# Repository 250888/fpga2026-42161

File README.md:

# 瞬迹（XunJi）— 基于 FPGA 的线束拓扑重建与 μs 级瞬态开路诊断装置

> 主控：EGO1 **Artix-7 XC7A35T-1CSG324C** @ 100 MHz ｜ 工具链：**Vivado 2026.1**
> 赛事：第十届全国大学生嵌入式芯片与系统设计竞赛 · FPGA 创新设计赛道（AMD）
> 许可证：[MIT](LICENSE)
> 大模型协作记录：[`report/llm-collaboration-log.md`](report/llm-collaboration-log.md) ｜ 技能包：[`skill/`](skill/)

## 一句话主线

**静态重建「线怎么接」，动态捕获「线什么时候断」。**

16 路逐路扫描重建 16×16 连接矩阵；与学习到的参考矩阵比对，输出五级故障判定
（PASS / OPEN / MISWIRE / BRIDGE / ANOMALY）并定位到具体线号；
再由 CD4066 阵列注入 μs 级瞬态断线，FPGA 以 100 MHz 采样捕获。

## 实测指标

| 指标 | 值 |
|---|---|
| 通道数 | 16 |
| 单轮扫描周期 | 112 μs |
| 帧长 / 波特率 / 帧率 | 48 B / 115200 bps / 240 fps |
| 资源（XC7A35T） | LUT **2119**（10.19%）· FF **1564**（3.76%）· BRAM 0 · DSP 0 |
| 时序 | WNS **+1.408 ns**，全部约束满足 |
| 回归 | iverilog 6/6 testbench · pytest **84** 项 |
| 实测结果 | 16/16 通道全通；四类故障（拔线/接反/短接/混合）全部正确分类并定位 |

## 快速开始

```bat
uv sync                                   :: 安装依赖（Python 3.12）
uv run pytest -q                          :: 全部测试（84 项）
uv run python -m xunji.cli sim            :: iverilog 仿真（6 个 testbench）
uv run python -m xunji.cli lint           :: RTL 风格检查
uv run python scripts\sync_to_build.py --build   :: 综合+实现，产出 .bit
```

> 注意：本机部分环境下 `uv run xunji` 启动器会被策略拦截，
> 请统一用 `uv run python -m xunji.cli <子命令>`。

烧录（EGO1，JTAG）：

```bat
C:\AMDDesignTools\2026.1\Vivado\bin\vivado.bat -mode batch -source scripts\program_ego1.tcl
```

> ⚠ JTAG 配置是**易失**的：每次断电/重新插拔后必须重新烧录。
> 且 LEARN 的参考矩阵存在 FPGA 寄存器里，重烧后需重新按学习键（板载 **S1**）。

## 目录结构

主办方推荐结构见指南 §3.3.5.4；本仓库**保留中文目录名**（更贴合队内协作习惯），
按指南「采用其他组织方式须给出目录对照说明」的要求对照如下：

| 本项目路径 | 作用 | 对应推荐结构 |
|---|---|---|
| `rtl/` | Verilog 源码（15 个文件） | `src/` |
| `sim/` | testbench（6 个） | `sim/` |
| `tests/` | pytest（84 项，含黄金帧回归） | `sim/`（验证） |
| `src/xunji/` | 主机侧 Python 包（协议解析 / CLI） | `src/`（软件） |
| `constrs/` | EGO1 XDC | `build/` |
| `scripts/` | Vivado Tcl · 构建 · 报告与海报生成 · 烧录 | `build/` |
| `pcb/` | 前端板参数化生成脚本 + KiCad 工程 + Gerber | `board/`（自制硬件） |
| `firmware/` | Arduino Nano 4066 脉冲源固件 | `board/` |
| `doc/` | 设计报告、上位机、证据 hex、原理图与 PCB 图、外壳模型 | `report/` + `data/` |
| **`skill/`** | **技能包（指南要求）** | `skill/` |
| **`report/`** | **大模型协作记录（指南要求）** | `report/` |

## 关键设计

### 双端有源扫描拓扑

```
a_ctrl_n → LVC07(开漏) → RS 330Ω → JA → 被测线束 → JB → RP 4.7kΩ 上拉
        → LVC14(施密特反相) → b_raw → FPGA
```

- A 端开漏激励：多路同时存在时不会发生推挽竞争；串阻把单路短路电流限制在约 10 mA
- B 端上拉 + 施密特反相：抑制长线束慢边沿抖动
- 仅用 32 根信号线完成 16×16 全连接矩阵重建

### 三层滤波

空闲稳定窗 500 周期（5 μs）→ 101 拍多数表决 → 8 拍去毛刺。

### 单时钟、纯 clock-enable

全系统仅 100 MHz 一个时钟域；`b_raw` / `uart_rx` 均经两级同步器；
复位经异步拉低、同步释放。

### 帧矩阵快照

在发送触发沿锁存矩阵，保证一帧内 CRC 与负载**同源**（这是本项目最重要的一个缺陷修复）。

## 故障判定语义

| cls | 含义 | 判据 |
|---|---|---|
| 0 | PASS | 与参考矩阵完全一致 |
| 3 | BRIDGE | 任一方向度 > 1（短接优先） |
| 2 | MISWIRE | 有缺失也有额外，且仍是双射（接反/换位） |
| 1 | OPEN | 只有缺失、没有额外，且缺失行实测为空 |
| 4 | ANOMALY | 混合、无法唯一解释（**不夸大**：拒绝硬套类型） |
| 5 | NO_REF | 尚未学习 |

## 硬件

- **主控**：EGO1（XC7A35T），100 MHz → P17，复位 P15，UART T4/N5
- **前端板 FE-16**：96×96 mm 双层板，LVC07×3 + LVC14×3 + 49 颗电阻 + 7 颗电容，
  JA/JB 为 2×10 接口，J5 2×18 与主控对接，TP1–TP50 测试点
- **故障注入**：CD4066 ×4（32 路开关）+ Arduino Nano

## 复现步骤（从零开始）

1. **装环境**：Python 3.12 + `uv`；Vivado 2026.1
2. **拉代码**：`git clone <repo>` → `uv sync`
3. **验软件**：`uv run pytest -q`（应 84 passed）→ `uv run python -m xunji.cli sim`（应 6/6 PASS）
4. **做硬件**：按 `pcb/frontend16/` 的脚本生成 Gerber 打板并焊装（BOM 见 `doc/`）
5. **出 bit**：`uv run python scripts\sync_to_build.py --build`
6. **上板**：烧录 `program_ego1.tcl` → 拨扫描开关 → 串口 115200 收帧
7. **学参考**：接 1:1 线束全通后，按板载 **S1** 学习 → `cls` 由 5 变 0
8. **做故障**：拔线 → `cls=1`；交换两根 → `cls=2`；短接两根 → `cls=3`
9. **看结果**：`uv run python -m xunji.cli read --port COM<x> --frames 3`

## 文档索引

| 文件 | 内容 |
|---|---|
| [`report/llm-collaboration-log.md`](report/llm-collaboration-log.md) | 大模型协作记录（提示词 / 自我纠错轨迹 / 失误清单） |
| [`skill/README.md`](skill/README.md) | 技能包索引与复用验证 |
| `doc/瞬迹_作品报告.pdf` | 作品设计报告（提交版） |
| `doc/瞬迹_海报_中英_终版.pptx` | **提交用海报（定稿，中英各一页）** |
| `doc/瞬迹_海报_中文版_含校徽.pdf` · `doc/XUNJI_Poster_English_含校徽.pdf` | 海报的 PDF 定稿（含校徽与队伍信息，仅用于上传与展示；决赛现场 A4 打印版需去掉队伍信息） |
| `doc/证据/` | 四类故障的原始帧证据（hex） |
| `doc/photous/` | 实物照片与演示截图 |
| `AGENTS.md` | 开发规范（AI 协作者必读） |

## 许可证

[MIT](LICENSE) —— 允许再分发，欢迎复用 `skill/` 中的经验。

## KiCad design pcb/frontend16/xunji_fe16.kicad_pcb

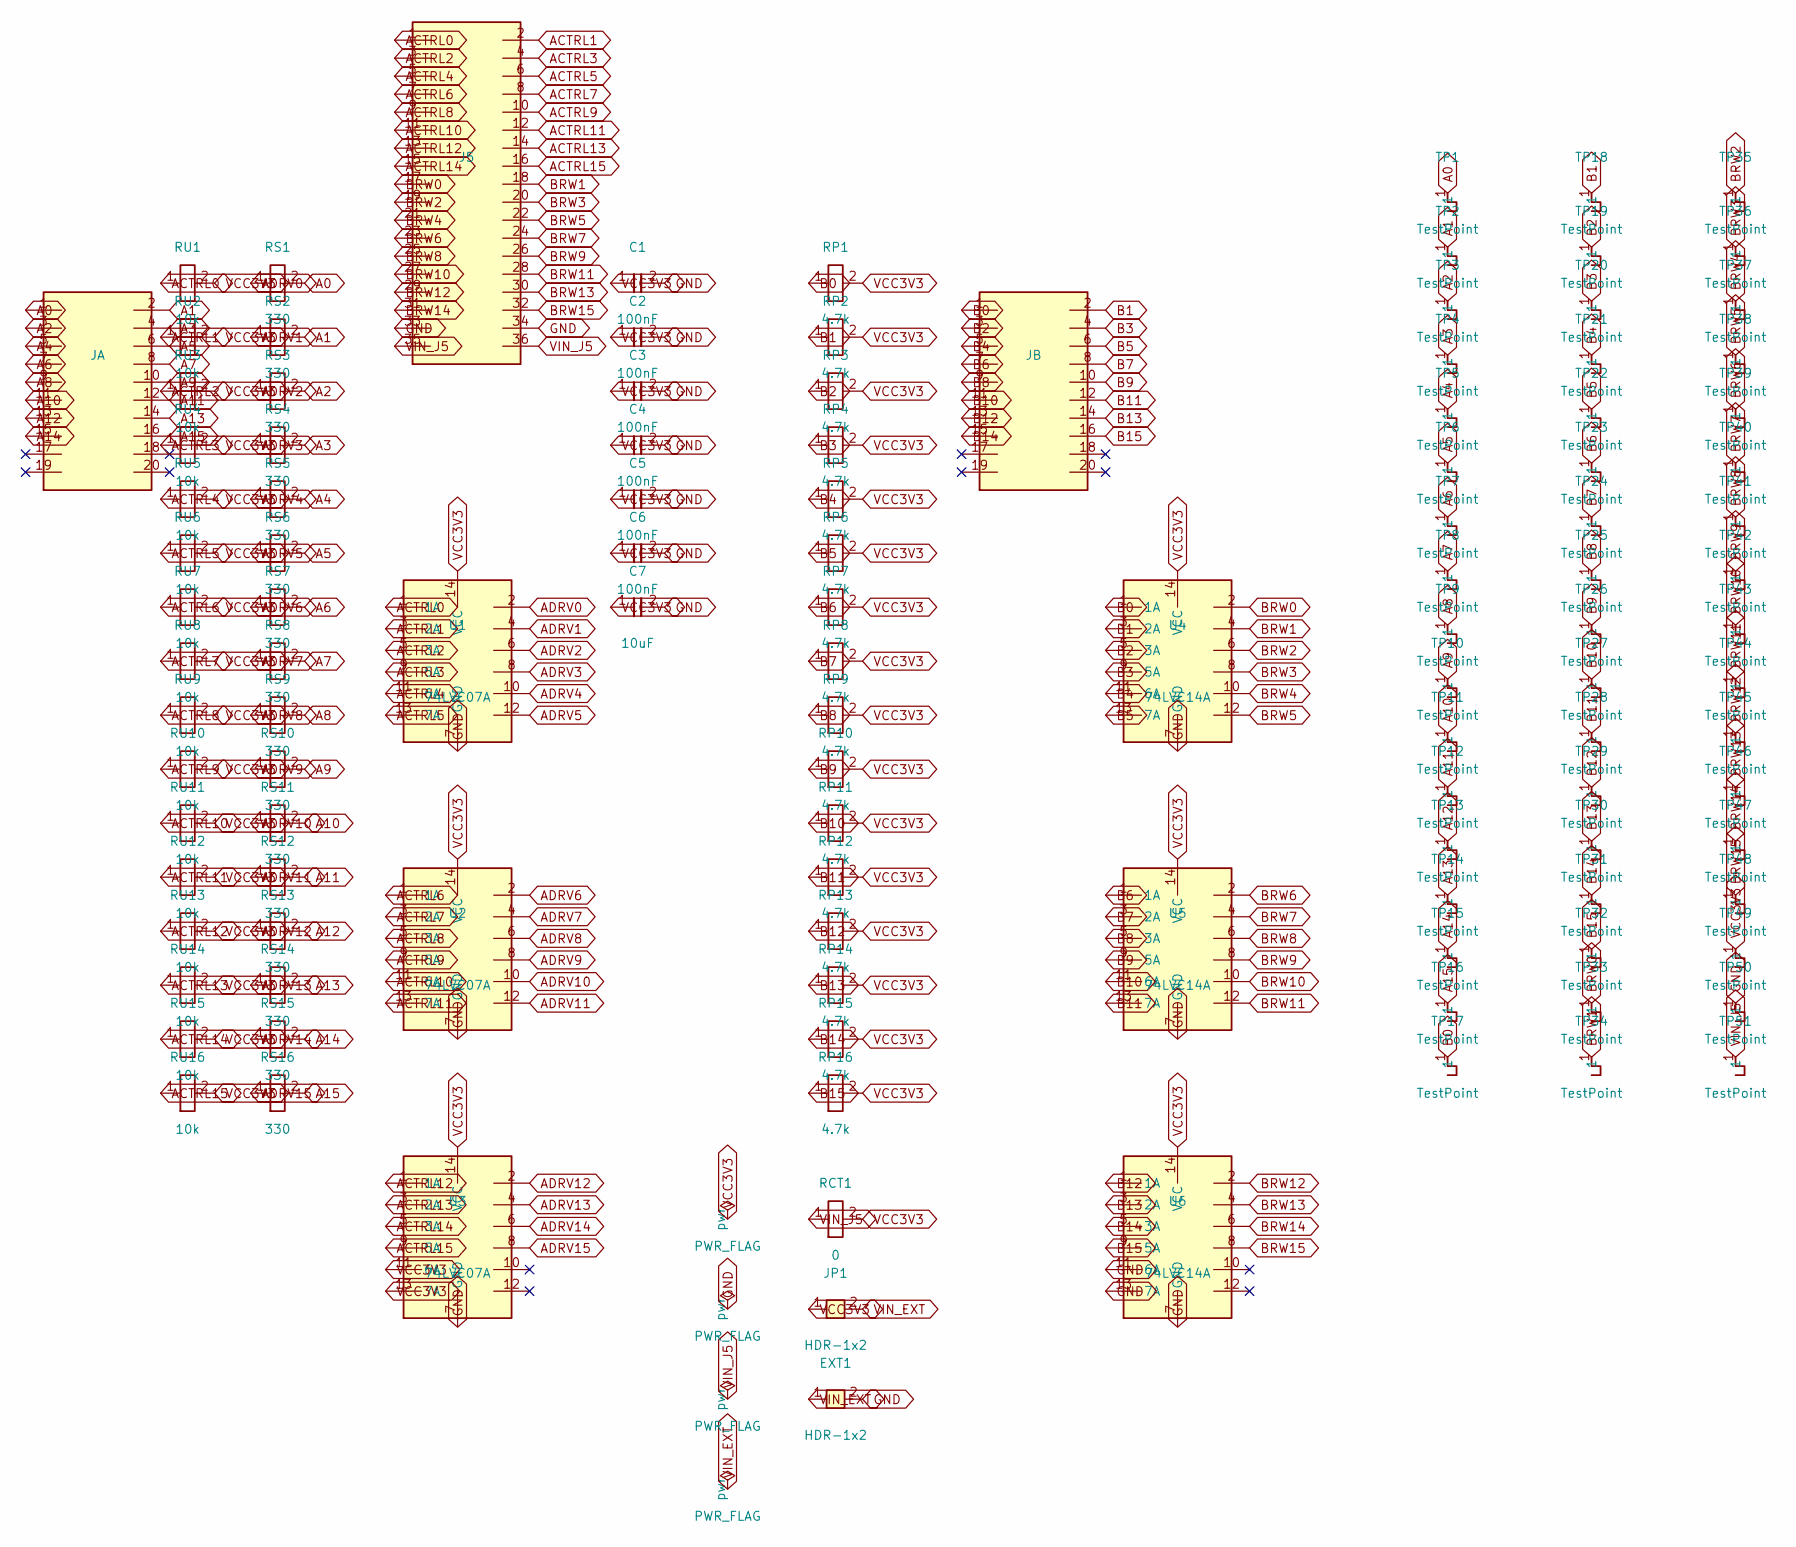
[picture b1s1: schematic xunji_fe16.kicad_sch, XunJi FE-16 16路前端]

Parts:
C1, C2, C3, C4, C5, C6: 100nF
C7: 10uF
EXT1: HDR-1x2
J5: (no value)
JA: (no value)
JB: (no value)
JP1: HDR-1x2
RCT1: 0
RP1, RP2, RP3, RP4, RP5, RP6, RP7, RP8, RP9, RP10, RP11, RP12, RP13, RP14, RP15, RP16: 4.7k
RS1, RS2, RS3, RS4, RS5, RS6, RS7, RS8, RS9, RS10, RS11, RS12, RS13, RS14, RS15, RS16: 330
RU1, RU2, RU3, RU4, RU5, RU6, RU7, RU8, RU9, RU10, RU11, RU12, RU13, RU14, RU15, RU16: 10k
TP1, TP2, TP3, TP4, TP5, TP6, TP7, TP8, TP9, TP10, TP11, TP12, TP13, TP14, TP15, TP16, TP17, TP18, TP19, TP20, TP21, TP22, TP23, TP24, TP25, TP26, TP27, TP28, TP29, TP30, TP31, TP32, TP33, TP34, TP35, TP36, TP37, TP38, TP39, TP40, TP41, TP42, TP43, TP44, TP45, TP46, TP47, TP48, TP49, TP50, TP51: TestPoint
U1, U2, U3: 74LVC07A
U4, U5, U6: 74LVC14A

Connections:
A0: JA.1, RS1.2, TP1.1
A1: JA.2, RS2.2, TP2.1
A2: JA.3, RS3.2, TP3.1
A3: JA.4, RS4.2, TP4.1
A4: JA.5, RS5.2, TP5.1
A5: JA.6, RS6.2, TP6.1
A6: JA.7, RS7.2, TP7.1
A7: JA.8, RS8.2, TP8.1
A8: JA.9, RS9.2, TP9.1
A9: JA.10, RS10.2, TP10.1
A10: JA.11, RS11.2, TP11.1
A11: JA.12, RS12.2, TP12.1
A12: JA.13, RS13.2, TP13.1
A13: JA.14, RS14.2, TP14.1
A14: JA.15, RS15.2, TP15.1
A15: JA.16, RS16.2, TP16.1
ACTRL0: J5.1, RU1.1, U1.1 (1A)
ACTRL1: J5.2, RU2.1, U1.3 (2A)
ACTRL2: J5.3, RU3.1, U1.5 (3A)
ACTRL3: J5.4, RU4.1, U1.9 (5A)
ACTRL4: J5.5, RU5.1, U1.11 (6A)
ACTRL5: J5.6, RU6.1, U1.13 (7A)
ACTRL6: J5.7, RU7.1, U2.1 (1A)
ACTRL7: J5.8, RU8.1, U2.3 (2A)
ACTRL8: J5.9, RU9.1, U2.5 (3A)
ACTRL9: J5.10, RU10.1, U2.9 (5A)
ACTRL10: J5.11, RU11.1, U2.11 (6A)
ACTRL11: J5.12, RU12.1, U2.13 (7A)
ACTRL12: J5.13, RU13.1, U3.1 (1A)
ACTRL13: J5.14, RU14.1, U3.3 (2A)
ACTRL14: J5.15, RU15.1, U3.5 (3A)
ACTRL15: J5.16, RU16.1, U3.9 (5A)
ADRV0: RS1.1, U1.2
ADRV1: RS2.1, U1.4
ADRV2: RS3.1, U1.6
ADRV3: RS4.1, U1.8
ADRV4: RS5.1, U1.10
ADRV5: RS6.1, U1.12
ADRV6: RS7.1, U2.2
ADRV7: RS8.1, U2.4
ADRV8: RS9.1, U2.6
ADRV9: RS10.1, U2.8
ADRV10: RS11.1, U2.10
ADRV11: RS12.1, U2.12
ADRV12: RS13.1, U3.2
ADRV13: RS14.1, U3.4
ADRV14: RS15.1, U3.6
ADRV15: RS16.1, U3.8
B0: JB.1, RP1.1, TP17.1, U4.1 (1A)
B1: JB.2, RP2.1, TP18.1, U4.3 (2A)
B2: JB.3, RP3.1, TP19.1, U4.5 (3A)
B3: JB.4, RP4.1, TP20.1, U4.9 (5A)
B4: JB.5, RP5.1, TP21.1, U4.11 (6A)
B5: JB.6, RP6.1, TP22.1, U4.13 (7A)
B6: JB.7, RP7.1, TP23.1, U5.1 (1A)
B7: JB.8, RP8.1, TP24.1, U5.3 (2A)
B8: JB.9, RP9.1, TP25.1, U5.5 (3A)
B9: JB.10, RP10.1, TP26.1, U5.9 (5A)
B10: JB.11, RP11.1, TP27.1, U5.11 (6A)
B11: JB.12, RP12.1, TP28.1, U5.13 (7A)
B12: JB.13, RP13.1, TP29.1, U6.1 (1A)
B13: JB.14, RP14.1, TP30.1, U6.3 (2A)
B14: JB.15, RP15.1, TP31.1, U6.5 (3A)
B15: JB.16, RP16.1, TP32.1, U6.9 (5A)
BRW0: J5.17, TP33.1, U4.2
BRW1: J5.18, TP34.1, U4.4
BRW2: J5.19, TP35.1, U4.6
BRW3: J5.20, TP36.1, U4.8
BRW4: J5.21, TP37.1, U4.10
BRW5: J5.22, TP38.1, U4.12
BRW6: J5.23, TP39.1, U5.2
BRW7: J5.24, TP40.1, U5.4
BRW8: J5.25, TP41.1, U5.6
BRW9: J5.26, TP42.1, U5.8
BRW10: J5.27, TP43.1, U5.10
BRW11: J5.28, TP44.1, U5.12
BRW12: J5.29, TP45.1, U6.2
BRW13: J5.30, TP46.1, U6.4
BRW14: J5.31, TP47.1, U6.6
BRW15: J5.32, TP48.1, U6.8
GND: C1.2, C2.2, C3.2, C4.2, C5.2, C6.2, C7.2, EXT1.2, J5.33, J5.34, TP50.1, U1.7 (GND), U2.7 (GND), U3.7 (GND), U4.7 (GND), U5.7 (GND), U6.7 (GND), U6.11 (6A), U6.13 (7A)
VCC3V3: C1.1, C2.1, C3.1, C4.1, C5.1, C6.1, C7.1, JP1.1, RCT1.2, RP1.2, RP2.2, RP3.2, RP4.2, RP5.2, RP6.2, RP7.2, RP8.2, RP9.2, RP10.2, RP11.2, RP12.2, RP13.2, RP14.2, RP15.2, RP16.2, RU1.2, RU2.2, RU3.2, RU4.2, RU5.2, RU6.2, RU7.2, RU8.2, RU9.2, RU10.2, RU11.2, RU12.2, RU13.2, RU14.2, RU15.2, RU16.2, TP49.1, U1.14 (VCC), U2.14 (VCC), U3.11 (6A), U3.13 (7A), U3.14 (VCC), U4.14 (VCC), U5.14 (VCC), U6.14 (VCC)
VIN_EXT: EXT1.1, JP1.2
VIN_J5: J5.35, J5.36, RCT1.1, TP51.1

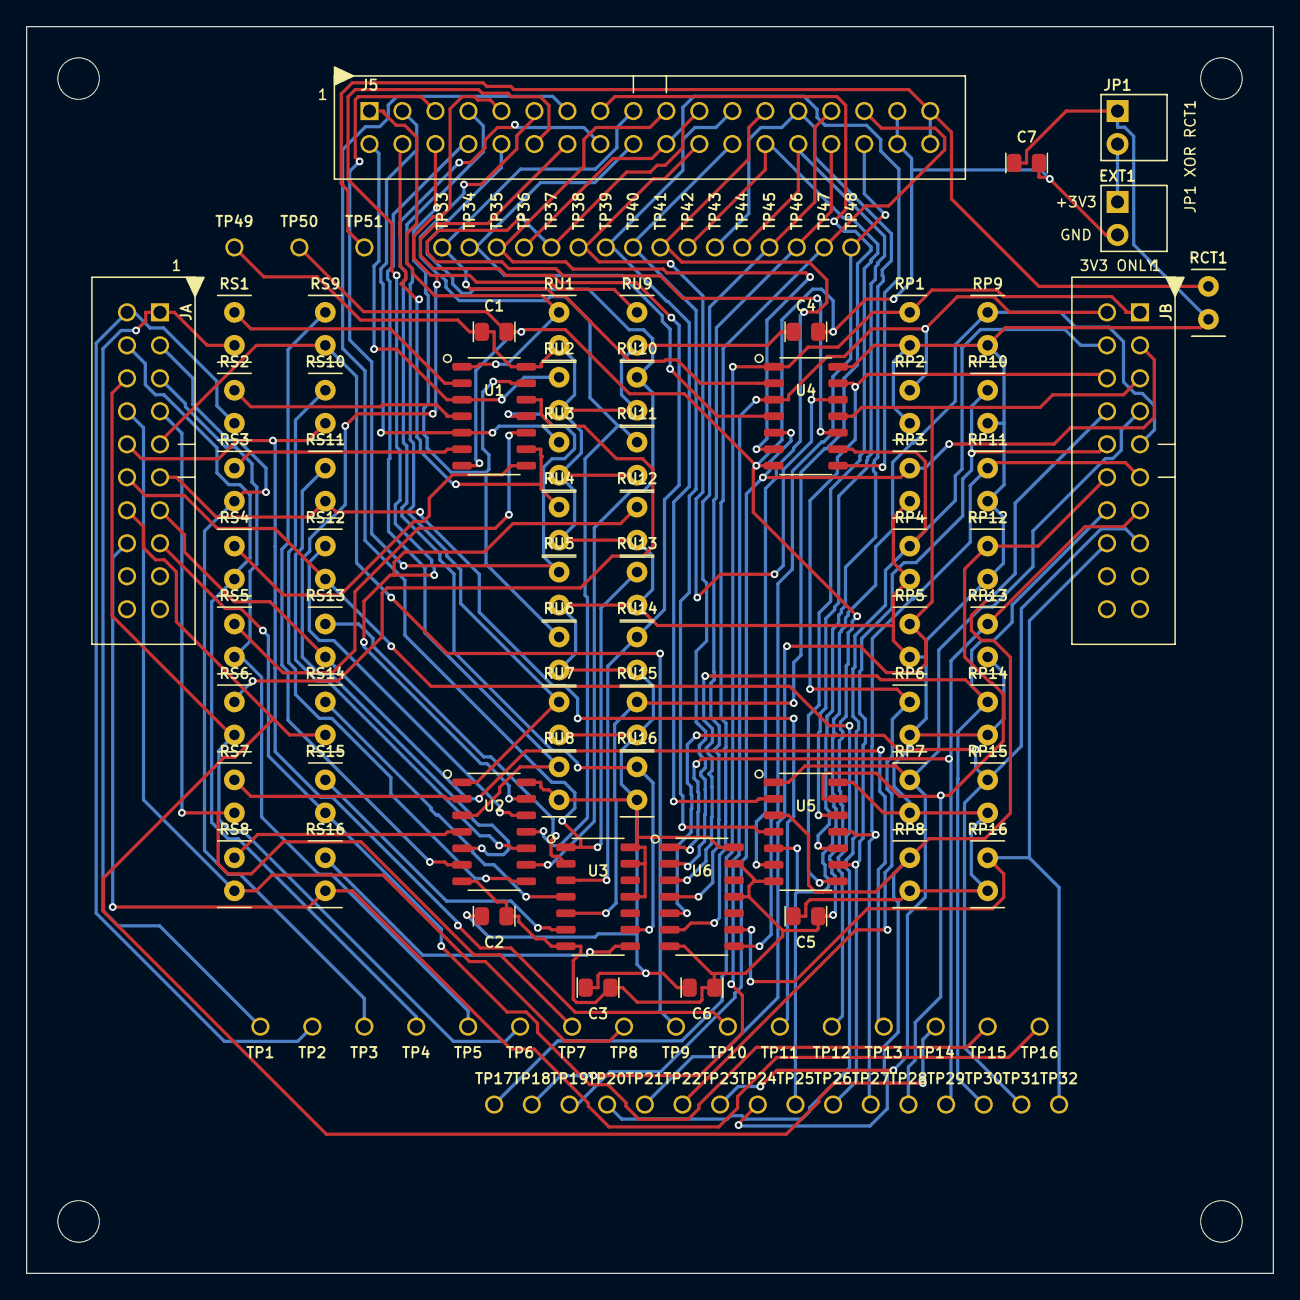
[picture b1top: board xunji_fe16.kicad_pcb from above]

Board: 2 copper layers, 96.0 x 96.0 mm, 122 parts (0 on the bottom side), 84 nets.

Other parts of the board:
H1, H2, H3, H4: MountingHole; MountingHole_3.2mm

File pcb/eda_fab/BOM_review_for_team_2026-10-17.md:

# xunji_fe16 板 BOM 采购审查清单（2026-10-17）

板型：xunji_fe16_1（FE16 探测器接口板）  
BOM：**11 组物料 / 67 件贴装与插件元件**（另有测试点 51 个、安装孔 4 个，不采购）  
全部物料已绑定立创商城编号。

## 一、BOM 明细

| # | 位号 | 值 | 封装 | 立创编号 | 数量 | 物料 | 贴装 |
|---|---|---|---|---|---|---|---|
| 1 | C1,C2,C3,C4,C5,C6 | 100nF | R_0805_2012Metric | C28233 | 6 | 100nF ±10% 100V X7R 0805（三星 CL21B104KCFNNNE） | 贴片(SMT) |
| 2 | C7 | 10uF | R_0805_2012Metric | C15850 | 1 | 10µF ±10% 25V X5R 0805（三星 CL21A106KAYNNNE） | 贴片(SMT) |
| 3 | EXT1,JP1 | HDR-1x2 | PinHeader_1x02_P2.54mm | C9900010030 | 2 | 2.54mm 单排排针 1x2 直插 | 插件(THT) |
| 4 | J5 | IDC-2x18 | IDC-Header_2x18_P2.54mm | C55160413 | 1 | 2.54mm IDC 简牛座 2x18 直插 | 插件(THT) |
| 5 | JA,JB | IDC-2x10 | IDC-Header_2x10_P2.54mm | C9900016201 | 2 | 2.54mm IDC 简牛座 2x10 直插 | 插件(THT) |
| 6 | RCT1 | 0 | R_0805_2012Metric | C17477 | 1 | 0Ω ±1% 125mW 0805 厚膜电阻 | 贴片(SMT) |
| 7 | RP1,RP2,RP3,RP4,RP5,RP6,RP7,RP8,RP9,RP10,RP11,RP12,RP13,RP14,RP15,RP16 | 4.7k | R_0805_2012Metric | C17673 | 16 | 4.7kΩ ±1% 125mW 0805 厚膜电阻 | 贴片(SMT) |
| 8 | RS1,RS2,RS3,RS4,RS5,RS6,RS7,RS8,RS9,RS10,RS11,RS12,RS13,RS14,RS15,RS16 | 330 | R_0805_2012Metric | C17630 | 16 | 330Ω ±1% 125mW 0805 厚膜电阻 | 贴片(SMT) |
| 9 | RU1,RU2,RU3,RU4,RU5,RU6,RU7,RU8,RU9,RU10,RU11,RU12,RU13,RU14,RU15,RU16 | 10k | R_0805_2012Metric | C17414 | 16 | 10kΩ ±1% 125mW 0805 厚膜电阻 | 贴片(SMT) |
| 10 | U1,U2,U3 | SN74LVC07A | SOIC-14_3.9x8.7mm_P1.27mm | C7659 | 3 | SN74LVC07ADR 六路开漏缓冲器 SOIC-14（TI） | 贴片(SMT) |
| 11 | U4,U5,U6 | SN74LVC14A | SOIC-14_3.9x8.7mm_P1.27mm | C133541 | 3 | SN74LVC14ADR 六路施密特反相器 SOIC-14（TI） | 贴片(SMT) |

## 二、审查结论（按原理图值逐项核对）

- **值与封装：11 组全部一致，未发现采购错误。** U1–U3 = 74LVC07A ↔ SN74LVC07A（SOIC-14）；U4–U6 = 74LVC14A ↔ SN74LVC14A（SOIC-14）；RU=10k、RS=330、RP=4.7k、RCT1=0Ω 与原理图值一致；C1–C6=100nF、C7=10µF 与原理图一致。
- **类型**：J5/JA/JB 为 IDC 排线座（简牛），JP1/EXT1 为 1x2 排针，均为 2.54mm **直插件**，不参与 SMT 贴片。

## 三、需要队友确认的点（不是错，是设计意图）

1. **电容耐压**：C1–C6 选了 100V、C7 选了 25V 的料（均为 Basic 库常规件）。若电源 ≤5V 可降额，但当前价格影响很小。
2. **U1–U3 开漏**：SN74LVC07A 是**开漏输出**（需要上拉电阻，见 RP 组）。若原意是推挽输出应为 74LVC07（无 A）——原理图标注的是 74LVC07A，按图采购没错，请确认设计本意。
3. **IDC 锁扣/防呆**：当前选的是标准简牛（无锁扣）。若线缆需要防脱落或防插反，请告知更换型号。
4. **JP1 与 RCT1 二选一**：JP1（1x2 跳线）与 RCT1（0Ω）是互斥配置，装配时只装一个。

## 四、生产文件

- Gerber：`Gerber_xunji_fe16_2026-10-17.zip`（9 层 + 3 钻孔 + 飞针 + PCB 信息，标准立创包）
- BOM：`BOM_xunji_fe16_2026_10_17.xlsx`（本清单同源）
- CPL：`PickAndPlace_xunji_fe16_2026_10_17.xlsx`（122 元件坐标，mm）
- 工程快照：`eda_project/xunji_fe16_kicad_2026-10-17_final.epro2`
